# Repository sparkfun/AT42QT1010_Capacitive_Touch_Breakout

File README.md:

SparkFun Capacitive Touch Breakout - AT42QT101X
====================================

<table class="table table-hover table-striped table-bordered">
  <tr>
   <td><a href="https://www.sparkfun.com/products/12041"><div align="center"></div></a></td>
  <td><a href="https://www.sparkfun.com/products/14520"><div align="center"></div></a></center></td>
  </tr>
  <tr>
    <td><div align="center">SparkFun Capacitive Touch Breakout - AT42QT1010 [<a href="https://www.sparkfun.com/products/12041">SEN-12041</a>]</div></td>
    <td><div align="center">SparkFun Capacitive Touch Breakout - AT42QT1011 [<a href="https://www.sparkfun.com/products/14520">SEN-14520</a>]</div></td>
  </tr>
</table>

If you need to add user input without using a button, then a capacitive touch interface might be the answer. The AT42QT1010 and AT42QT1011 Capacitive Touch Breakout boards offer a single capacitive touch button with easy-to-use digital I/O pins. Each model features a slightly different output duration.

Repository Contents
-------------------
* **/Documentation** - Datasheet
* **/Firmware** - Example Arduino sketches
* **/Hardware** - All Eagle design files (.brd, .sch, .STL)
* **/Libraries** - Eagle part library
* **/Production** - Test bed files and production panel files

Documentation
-------------------

* **[Hookup Guide](https://learn.sparkfun.com/tutorials/at42qt101x-capacitive-touch-breakout-hookup-guide)** - Basic hookup guide for the AT42QT1010 and AT42QT1011 Capacitive Touch Breakout.
* *[Hookup Guide (RETIRED)](https://learn.sparkfun.com/tutorials/at42qt1010-capacitive-touch-breakout-hookup-guide) - Basic hookup guide for the AT42QT1010 Capacitive Touch Breakout.*
* **[SparkFun Fritzing repo](https://github.com/sparkfun/Fritzing_Parts)** - Fritzing diagrams for SparkFun products.

Version History
---------------
* **HW_v20.0_FW_v1.0** - Current Version for AT42QT1010 and AT42QT1011 with 8-pin UDFN/USON package.
* *[HW_v1.0_FW_v1.0 (RETIRED)](https://github.com/sparkfun/AT42QT1010_Capacitive_Touch_Breakout/releases/tag/HW_v1.0_FW_v1.0) - Initial release for the AT42QT1010 with 6-Pin SOT23-6 package.*

License Information
-------------------

This product is _**open source**_! 

Please review the LICENSE.md file for license information. 

If you have any questions or concerns on licensing, please contact techsupport@sparkfun.com.

Distributed as-is; no warranty is given.

- Your friends at SparkFun.

_<COLLABORATION CREDIT>_

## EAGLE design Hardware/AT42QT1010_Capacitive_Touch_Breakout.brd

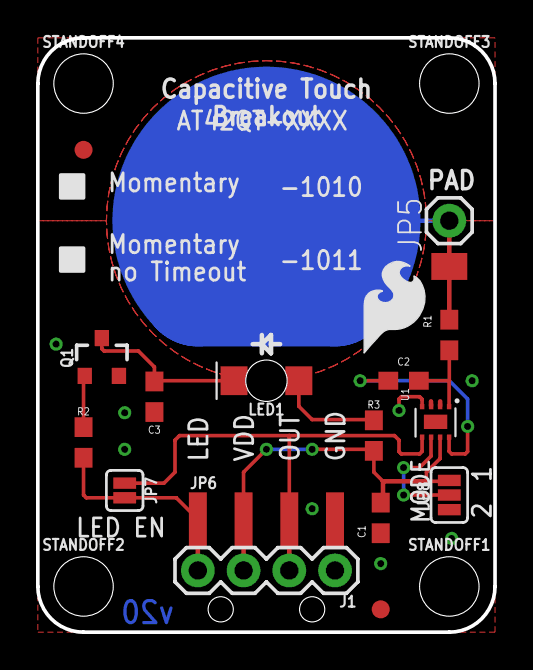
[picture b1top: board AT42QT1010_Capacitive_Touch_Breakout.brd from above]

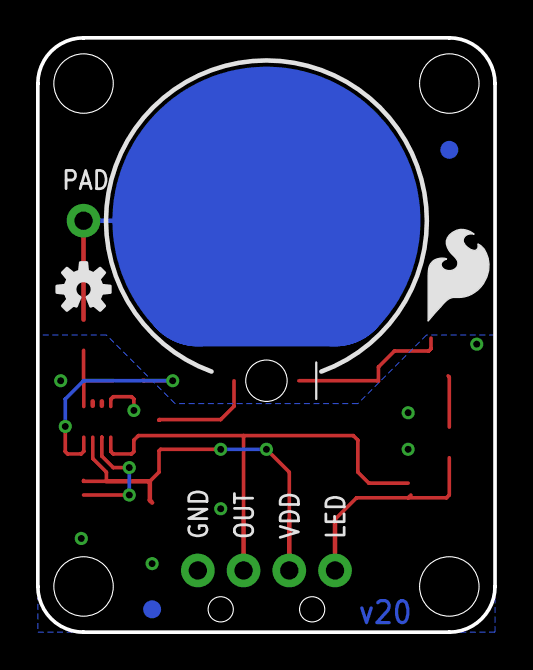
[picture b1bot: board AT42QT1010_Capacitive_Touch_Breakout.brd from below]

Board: 2 copper layers, 25.4 x 33.0 mm, 28 parts (4 on the bottom side), 11 nets.

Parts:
C1: 0.1uF; 0603
C2, C3: 10nF; 0603
FID1, FID2, FID3, FID4: FIDUCIAL1X2; FIDUCIAL-1X2
FRAME1: FRAME-LETTER; CREATIVE_COMMONS
J1: 1X04
JP5: 1X01
JP6: SMD; 1X04_SMD_RA_MALE
JP7: JUMPER-SMT_2_NC_PASTE_SILK; SMT-JUMPER_2_NC_PASTE_SILK
JP8: JUMPER-SMT_3_1-NC_PASTE_SILK; SMT-JUMPER_3_1-NC_PASTE_SILK
JP9: M01SMD-4.5X1.5; PAD-1.5X4.5
LED1: Green; LED-1206-BOTTOM
LOGO1, LOGO4: SFE_LOGO_FLAME.2_INCH; SFE_LOGO_FLAME_.2
LOGO2: OSHW-LOGOS; OSHW-LOGO-S
Q1: 600mA/40V; SOT23-3
R1: 10k; 0603
R2: 2.2k; 0603
R3: 200; 0603
STANDOFF1, STANDOFF2, STANDOFF3, STANDOFF4: STAND-OFF
U1: AT42QT1010 - UDFN; UDFN/USON_8_PAD
U$1: SPECIAL_INSTRUCTIONS-ORDERING; ORDERING_INSTRUCTIONS

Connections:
GND: C1.2, C3.2, J1.1, JP6.4, JP8.1, Q1.2, U1.4
LED: J1.4, JP6.1, JP7.2, R2.1
unnamed: JP8.2, U1.6
unnamed: C2.2, U1.8
unnamed: C2.1, R1.1, U1.1
unnamed: Q1.1, R2.2
unnamed: C3.1, LED1.C, Q1.3
unnamed: LED1.A, R3.1
OUT: J1.2, JP6.3, JP7.1, U1.5
PAD: JP5.1, JP9.P$1, R1.2
VCC: C1.1, J1.3, JP6.2, JP8.3, R3.2, U1.7

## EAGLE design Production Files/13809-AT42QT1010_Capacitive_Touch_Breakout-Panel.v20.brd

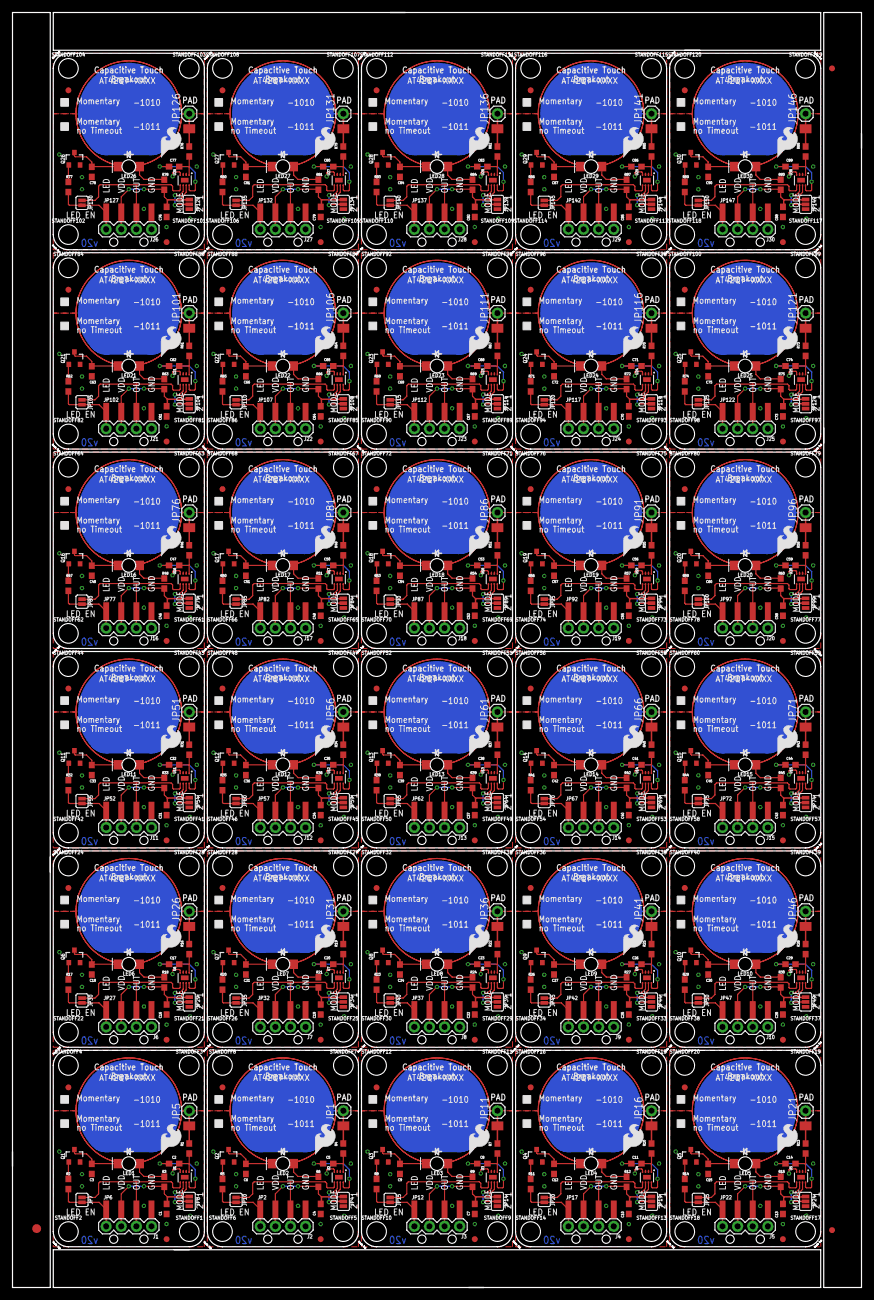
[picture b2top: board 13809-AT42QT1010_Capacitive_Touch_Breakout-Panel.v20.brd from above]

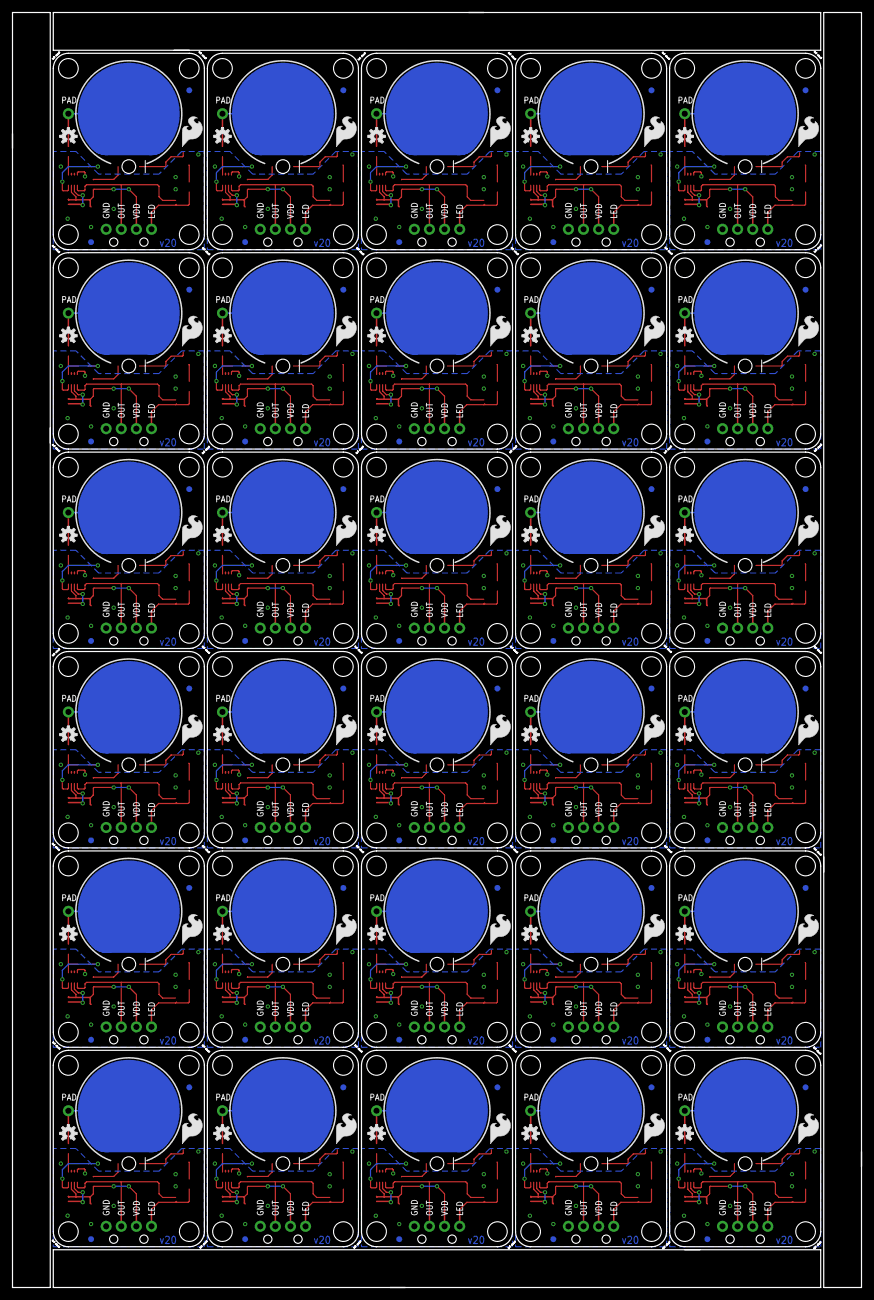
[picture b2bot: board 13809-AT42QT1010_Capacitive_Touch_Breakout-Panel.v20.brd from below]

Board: 2 copper layers, 142.7 x 214.4 mm, 783 parts (120 on the bottom side), 330 nets.

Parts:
C1, C4, C7, C10, C13, C16, C19, C22, C25, C28, C31, C34, C37, C40, C43, C46, C49, C52, C55, C58, C61, C64, C67, C70, C73, C76, C79, C82, C85, C88: 0.1uF; 0603
C2, C3, C5, C6, C8, C9, C11, C12, C14, C15, C17, C18, C20, C21, C23, C24, C26, C27, C29, C30, C32, C33, C35, C36, C38, C39, C41, C42, C44, C45, C47, C48, C50, C51, C53, C54, C56, C57, C59, C60, C62, C63, C65, C66, C68, C69, C71, C72, C74, C75, C77, C78, C80, C81, C83, C84, C86, C87, C89, C90: 10nF; 0603
E$1: FIDUCIAL-1.5X3
E$7, E$8: FIDUCIAL-1X2
FID1, FID2, FID3, FID4, FID5, FID6, FID7, FID8, FID9, FID10, FID11, FID12, FID13, FID14, FID15, FID16, FID17, FID18, FID19, FID20, FID21, FID22, FID23, FID24, FID25, FID26, FID27, FID28, FID29, FID30, FID31, FID32, FID33, FID34, FID35, FID36, FID37, FID38, FID39, FID40, FID41, FID42, FID43, FID44, FID45, FID46, FID47, FID48, FID49, FID50, FID51, FID52, FID53, FID54, FID55, FID56, FID57, FID58, FID59, FID60, FID61, FID62, FID63, FID64, FID65, FID66, FID67, FID68, FID69, FID70, FID71, FID72, FID73, FID74, FID75, FID76, FID77, FID78, FID79, FID80, FID81, FID82, FID83, FID84, FID85, FID86, FID87, FID88, FID89, FID90, FID91, FID92, FID93, FID94, FID95, FID96, FID97, FID98, FID99, FID100, FID101, FID102, FID103, FID104, FID105, FID106, FID107, FID108, FID109, FID110, FID111, FID112, FID113, FID114, FID115, FID116, FID117, FID118, FID119, FID120: FIDUCIAL1X2; FIDUCIAL-1X2
J1, J2, J3, J4, J5, J6, J7, J8, J9, J10, J11, J12, J13, J14, J15, J16, J17, J18, J19, J20, J21, J22, J23, J24, J25, J26, J27, J28, J29, J30: 1X04
JP1, JP5, JP11, JP16, JP21, JP26, JP31, JP36, JP41, JP46, JP51, JP56, JP61, JP66, JP71, JP76, JP81, JP86, JP91, JP96, JP101, JP106, JP111, JP116, JP121, JP126, JP131, JP136, JP141, JP146: 1X01
JP2, JP6, JP12, JP17, JP22, JP27, JP32, JP37, JP42, JP47, JP52, JP57, JP62, JP67, JP72, JP77, JP82, JP87, JP92, JP97, JP102, JP107, JP112, JP117, JP122, JP127, JP132, JP137, JP142, JP147: SMD; 1X04_SMD_RA_MALE
JP3, JP9, JP13, JP18, JP23, JP28, JP33, JP38, JP43, JP48, JP53, JP58, JP63, JP68, JP73, JP78, JP83, JP88, JP93, JP98, JP103, JP108, JP113, JP118, JP123, JP128, JP133, JP138, JP143, JP148: M01SMD-4.5X1.5; PAD-1.5X4.5
JP4, JP8, JP14, JP19, JP24, JP29, JP34, JP39, JP44, JP49, JP54, JP59, JP64, JP69, JP74, JP79, JP84, JP89, JP94, JP99, JP104, JP109, JP114, JP119, JP124, JP129, JP134, JP139, JP144, JP149: JUMPER-SMT_3_NO_SILK; SMT-JUMPER_3_NO_SILK
JP7, JP10, JP15, JP20, JP25, JP30, JP35, JP40, JP45, JP50, JP55, JP60, JP65, JP70, JP75, JP80, JP85, JP90, JP95, JP100, JP105, JP110, JP115, JP120, JP125, JP130, JP135, JP140, JP145, JP150: JUMPER-SMT_2_NO_SILK; SMT-JUMPER_2_NO_SILK
LED1, LED2, LED3, LED4, LED5, LED6, LED7, LED8, LED9, LED10, LED11, LED12, LED13, LED14, LED15, LED16, LED17, LED18, LED19, LED20, LED21, LED22, LED23, LED24, LED25, LED26, LED27, LED28, LED29, LED30: Green; LED-1206-BOTTOM
LOGO1, LOGO4, LOGO5, LOGO6, LOGO8, LOGO9, LOGO11, LOGO12, LOGO14, LOGO15, LOGO17, LOGO18, LOGO20, LOGO21, LOGO23, LOGO24, LOGO26, LOGO27, LOGO29, LOGO30, LOGO32, LOGO33, LOGO35, LOGO36, LOGO38, LOGO39, LOGO41, LOGO42, LOGO44, LOGO45, LOGO47, LOGO48, LOGO50, LOGO51, LOGO53, LOGO54, LOGO56, LOGO57, LOGO59, LOGO60, LOGO62, LOGO63, LOGO65, LOGO66, LOGO68, LOGO69, LOGO71, LOGO72, LOGO74, LOGO75, LOGO77, LOGO78, LOGO80, LOGO81, LOGO83, LOGO84, LOGO86, LOGO87, LOGO89, LOGO90: SFE_LOGO_FLAME.2_INCH; SFE_LOGO_FLAME_.2
LOGO2, LOGO3, LOGO7, LOGO10, LOGO13, LOGO16, LOGO19, LOGO22, LOGO25, LOGO28, LOGO31, LOGO34, LOGO37, LOGO40, LOGO43, LOGO46, LOGO49, LOGO52, LOGO55, LOGO58, LOGO61, LOGO64, LOGO67, LOGO70, LOGO73, LOGO76, LOGO79, LOGO82, LOGO85, LOGO88: OSHW-LOGOS; OSHW-LOGO-S
Q1, Q2, Q3, Q4, Q5, Q6, Q7, Q8, Q9, Q10, Q11, Q12, Q13, Q14, Q15, Q16, Q17, Q18, Q19, Q20, Q21, Q22, Q23, Q24, Q25, Q26, Q27, Q28, Q29, Q30: 600mA/40V; SOT23-3
R1, R4, R7, R10, R13, R16, R19, R22, R25, R28, R31, R34, R37, R40, R43, R46, R49, R52, R55, R58, R61, R64, R67, R70, R73, R76, R79, R82, R85, R88: 10k; 0603
R2, R5, R8, R11, R14, R17, R20, R23, R26, R29, R32, R35, R38, R41, R44, R47, R50, R53, R56, R59, R62, R65, R68, R71, R74, R77, R80, R83, R86, R89: 2.2k; 0603
R3, R6, R9, R12, R15, R18, R21, R24, R27, R30, R33, R36, R39, R42, R45, R48, R51, R54, R57, R60, R63, R66, R69, R72, R75, R78, R81, R84, R87, R90: 200; 0603
STANDOFF1, STANDOFF2, STANDOFF3, STANDOFF4, STANDOFF5, STANDOFF6, STANDOFF7, STANDOFF8, STANDOFF9, STANDOFF10, STANDOFF11, STANDOFF12, STANDOFF13, STANDOFF14, STANDOFF15, STANDOFF16, STANDOFF17, STANDOFF18, STANDOFF19, STANDOFF20, STANDOFF21, STANDOFF22, STANDOFF23, STANDOFF24, STANDOFF25, STANDOFF26, STANDOFF27, STANDOFF28, STANDOFF29, STANDOFF30, STANDOFF31, STANDOFF32, STANDOFF33, STANDOFF34, STANDOFF35, STANDOFF36, STANDOFF37, STANDOFF38, STANDOFF39, STANDOFF40, STANDOFF41, STANDOFF42, STANDOFF43, STANDOFF44, STANDOFF45, STANDOFF46, STANDOFF47, STANDOFF48, STANDOFF49, STANDOFF50, STANDOFF51, STANDOFF52, STANDOFF53, STANDOFF54, STANDOFF55, STANDOFF56, STANDOFF57, STANDOFF58, STANDOFF59, STANDOFF60, STANDOFF61, STANDOFF62, STANDOFF63, STANDOFF64, STANDOFF65, STANDOFF66, STANDOFF67, STANDOFF68, STANDOFF69, STANDOFF70, STANDOFF71, STANDOFF72, STANDOFF73, STANDOFF74, STANDOFF75, STANDOFF76, STANDOFF77, STANDOFF78, STANDOFF79, STANDOFF80, STANDOFF81, STANDOFF82, STANDOFF83, STANDOFF84, STANDOFF85, STANDOFF86, STANDOFF87, STANDOFF88, STANDOFF89, STANDOFF90, STANDOFF91, STANDOFF92, STANDOFF93, STANDOFF94, STANDOFF95, STANDOFF96, STANDOFF97, STANDOFF98, STANDOFF99, STANDOFF100, STANDOFF101, STANDOFF102, STANDOFF103, STANDOFF104, STANDOFF105, STANDOFF106, STANDOFF107, STANDOFF108, STANDOFF109, STANDOFF110, STANDOFF111, STANDOFF112, STANDOFF113, STANDOFF114, STANDOFF115, STANDOFF116, STANDOFF117, STANDOFF118, STANDOFF119, STANDOFF120: STAND-OFF
U1, U2, U3, U4, U5, U6, U7, U8, U9, U10, U11, U12, U13, U14, U15, U16, U17, U18, U19, U20, U21, U22, U23, U24, U25, U26, U27, U28, U29, U30: AT42QT1010 - UDFN; UDFN/USON_8_PAD

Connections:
GND: C1.2, C3.2, J1.1, JP6.4, JP8.3, Q1.2, U1.4
GND1: C4.2, C6.2, J2.1, JP2.4, JP4.3, Q2.2, U2.4
GND2: C7.2, C9.2, J3.1, JP12.4, JP14.3, Q3.2, U3.4
GND3: C10.2, C12.2, J4.1, JP17.4, JP19.3, Q4.2, U4.4
GND4: C13.2, C15.2, J5.1, JP22.4, JP24.3, Q5.2, U5.4
GND5: C16.2, C18.2, J6.1, JP27.4, JP29.3, Q6.2, U6.4
GND6: C19.2, C21.2, J7.1, JP32.4, JP34.3, Q7.2, U7.4
GND7: C22.2, C24.2, J8.1, JP37.4, JP39.3, Q8.2, U8.4
GND8: C25.2, C27.2, J9.1, JP42.4, JP44.3, Q9.2, U9.4
GND9: C28.2, C30.2, J10.1, JP47.4, JP49.3, Q10.2, U10.4
GND10: C31.2, C33.2, J11.1, JP52.4, JP54.3, Q11.2, U11.4
GND11: C34.2, C36.2, J12.1, JP57.4, JP59.3, Q12.2, U12.4
GND12: C37.2, C39.2, J13.1, JP62.4, JP64.3, Q13.2, U13.4
GND13: C40.2, C42.2, J14.1, JP67.4, JP69.3, Q14.2, U14.4
GND14: C43.2, C45.2, J15.1, JP72.4, JP74.3, Q15.2, U15.4
GND15: C46.2, C48.2, J16.1, JP77.4, JP79.3, Q16.2, U16.4
GND16: C49.2, C51.2, J17.1, JP82.4, JP84.3, Q17.2, U17.4
GND17: C52.2, C54.2, J18.1, JP87.4, JP89.3, Q18.2, U18.4
GND18: C55.2, C57.2, J19.1, JP92.4, JP94.3, Q19.2, U19.4
GND19: C58.2, C60.2, J20.1, JP97.4, JP99.3, Q20.2, U20.4
GND20: C61.2, C63.2, J21.1, JP102.4, JP104.3, Q21.2, U21.4
GND21: C64.2, C66.2, J22.1, JP107.4, JP109.3, Q22.2, U22.4
GND22: C67.2, C69.2, J23.1, JP112.4, JP114.3, Q23.2, U23.4
GND23: C70.2, C72.2, J24.1, JP117.4, JP119.3, Q24.2, U24.4
GND24: C73.2, C75.2, J25.1, JP122.4, JP124.3, Q25.2, U25.4
GND25: C76.2, C78.2, J26.1, JP127.4, JP129.3, Q26.2, U26.4
GND26: C79.2, C81.2, J27.1, JP132.4, JP134.3, Q27.2, U27.4
GND27: C82.2, C84.2, J28.1, JP137.4, JP139.3, Q28.2, U28.4
GND28: C85.2, C87.2, J29.1, JP142.4, JP144.3, Q29.2, U29.4
GND29: C88.2, C90.2, J30.1, JP147.4, JP149.3, Q30.2, U30.4
LED: J1.4, JP6.1, JP7.2, R2.1
LED1: J2.4, JP2.1, JP10.2, R5.1
LED2: J3.4, JP12.1, JP15.2, R8.1
LED3: J4.4, JP17.1, JP20.2, R11.1
LED4: J5.4, JP22.1, JP25.2, R14.1
LED5: J6.4, JP27.1, JP30.2, R17.1
LED6: J7.4, JP32.1, JP35.2, R20.1
LED7: J8.4, JP37.1, JP40.2, R23.1
LED8: J9.4, JP42.1, JP45.2, R26.1
LED9: J10.4, JP47.1, JP50.2, R29.1
LED10: J11.4, JP52.1, JP55.2, R32.1
LED11: J12.4, JP57.1, JP60.2, R35.1
LED12: J13.4, JP62.1, JP65.2, R38.1
LED13: J14.4, JP67.1, JP70.2, R41.1
LED14: J15.4, JP72.1, JP75.2, R44.1
LED15: J16.4, JP77.1, JP80.2, R47.1
LED16: J17.4, JP82.1, JP85.2, R50.1
LED17: J18.4, JP87.1, JP90.2, R53.1
LED18: J19.4, JP92.1, JP95.2, R56.1
LED19: J20.4, JP97.1, JP100.2, R59.1
LED20: J21.4, JP102.1, JP105.2, R62.1
LED21: J22.4, JP107.1, JP110.2, R65.1
LED22: J23.4, JP112.1, JP115.2, R68.1
LED23: J24.4, JP117.1, JP120.2, R71.1
LED24: J25.4, JP122.1, JP125.2, R74.1
LED25: J26.4, JP127.1, JP130.2, R77.1
LED26: J27.4, JP132.1, JP135.2, R80.1
LED27: J28.4, JP137.1, JP140.2, R83.1
LED28: J29.4, JP142.1, JP145.2, R86.1
LED29: J30.4, JP147.1, JP150.2, R89.1
unnamed: C5.2, U2.8
unnamed: C2.2, U1.8
unnamed: C2.1, R1.1, U1.1
unnamed: C5.1, R4.1, U2.1
unnamed: JP8.2, U1.6
unnamed: JP4.2, U2.6
unnamed: Q2.1, R5.2
unnamed: Q1.1, R2.2
unnamed: C3.1, LED1.C, Q1.3
unnamed: LED1.A, R3.1
unnamed: C6.1, LED2.C, Q2.3
unnamed: LED2.A, R6.1
unnamed: C8.2, U3.8
unnamed: C8.1, R7.1, U3.1
unnamed: JP14.2, U3.6
unnamed: Q3.1, R8.2
unnamed: C9.1, LED3.C, Q3.3
unnamed: LED3.A, R9.1
unnamed: C11.2, U4.8
unnamed: C11.1, R10.1, U4.1
unnamed: JP19.2, U4.6
unnamed: Q4.1, R11.2
unnamed: C12.1, LED4.C, Q4.3
unnamed: LED4.A, R12.1
unnamed: C14.2, U5.8
unnamed: C14.1, R13.1, U5.1
unnamed: JP24.2, U5.6
unnamed: Q5.1, R14.2
unnamed: C15.1, LED5.C, Q5.3
unnamed: LED5.A, R15.1
unnamed: C17.2, U6.8
unnamed: C17.1, R16.1, U6.1
unnamed: JP29.2, U6.6
unnamed: Q6.1, R17.2
unnamed: C18.1, LED6.C, Q6.3
unnamed: LED6.A, R18.1
unnamed: C20.2, U7.8
unnamed: C20.1, R19.1, U7.1
unnamed: JP34.2, U7.6
unnamed: Q7.1, R20.2
unnamed: C21.1, LED7.C, Q7.3
unnamed: LED7.A, R21.1
unnamed: C23.2, U8.8
unnamed: C23.1, R22.1, U8.1
unnamed: JP39.2, U8.6
unnamed: Q8.1, R23.2
unnamed: C24.1, LED8.C, Q8.3
unnamed: LED8.A, R24.1
unnamed: C26.2, U9.8
unnamed: C26.1, R25.1, U9.1
unnamed: JP44.2, U9.6
unnamed: Q9.1, R26.2
unnamed: C27.1, LED9.C, Q9.3
unnamed: LED9.A, R27.1
unnamed: C29.2, U10.8
unnamed: C29.1, R28.1, U10.1
unnamed: JP49.2, U10.6
unnamed: Q10.1, R29.2
unnamed: C30.1, LED10.C, Q10.3
unnamed: LED10.A, R30.1
unnamed: C32.2, U11.8
unnamed: C32.1, R31.1, U11.1
unnamed: JP54.2, U11.6
unnamed: Q11.1, R32.2
unnamed: C33.1, LED11.C, Q11.3
unnamed: LED11.A, R33.1
unnamed: C35.2, U12.8
unnamed: C35.1, R34.1, U12.1
unnamed: JP59.2, U12.6
unnamed: Q12.1, R35.2
unnamed: C36.1, LED12.C, Q12.3
unnamed: LED12.A, R36.1
unnamed: C38.2, U13.8
unnamed: C38.1, R37.1, U13.1
unnamed: JP64.2, U13.6
unnamed: Q13.1, R38.2
unnamed: C39.1, LED13.C, Q13.3
unnamed: LED13.A, R39.1
unnamed: C41.2, U14.8
unnamed: C41.1, R40.1, U14.1
unnamed: JP69.2, U14.6
unnamed: Q14.1, R41.2
unnamed: C42.1, LED14.C, Q14.3
unnamed: LED14.A, R42.1
unnamed: C44.2, U15.8
unnamed: C44.1, R43.1, U15.1
unnamed: JP74.2, U15.6
unnamed: Q15.1, R44.2
unnamed: C45.1, LED15.C, Q15.3
unnamed: LED15.A, R45.1
unnamed: C47.2, U16.8
unnamed: C47.1, R46.1, U16.1
unnamed: JP79.2, U16.6
unnamed: Q16.1, R47.2
unnamed: C48.1, LED16.C, Q16.3
unnamed: LED16.A, R48.1
unnamed: C50.2, U17.8
unnamed: C50.1, R49.1, U17.1
unnamed: JP84.2, U17.6
unnamed: Q17.1, R50.2
unnamed: C51.1, LED17.C, Q17.3
unnamed: LED17.A, R51.1
unnamed: C53.2, U18.8
unnamed: C53.1, R52.1, U18.1
unnamed: JP89.2, U18.6
unnamed: Q18.1, R53.2
unnamed: C54.1, LED18.C, Q18.3
unnamed: LED18.A, R54.1
unnamed: C56.2, U19.8
unnamed: C56.1, R55.1, U19.1
unnamed: JP94.2, U19.6
unnamed: Q19.1, R56.2
unnamed: C57.1, LED19.C, Q19.3
unnamed: LED19.A, R57.1
unnamed: C59.2, U20.8
unnamed: C59.1, R58.1, U20.1
unnamed: JP99.2, U20.6
unnamed: Q20.1, R59.2
unnamed: C60.1, LED20.C, Q20.3
unnamed: LED20.A, R60.1
unnamed: C62.2, U21.8
unnamed: C62.1, R61.1, U21.1
unnamed: JP104.2, U21.6
unnamed: Q21.1, R62.2
unnamed: C63.1, LED21.C, Q21.3
unnamed: LED21.A, R63.1
unnamed: C65.2, U22.8
unnamed: C65.1, R64.1, U22.1
unnamed: JP109.2, U22.6
unnamed: Q22.1, R65.2
unnamed: C66.1, LED22.C, Q22.3
unnamed: LED22.A, R66.1
unnamed: C68.2, U23.8
unnamed: C68.1, R67.1, U23.1
unnamed: JP114.2, U23.6
unnamed: Q23.1, R68.2
unnamed: C69.1, LED23.C, Q23.3
unnamed: LED23.A, R69.1
unnamed: C71.2, U24.8
unnamed: C71.1, R70.1, U24.1
unnamed: JP119.2, U24.6
unnamed: Q24.1, R71.2
unnamed: C72.1, LED24.C, Q24.3
unnamed: LED24.A, R72.1
unnamed: C74.2, U25.8
unnamed: C74.1, R73.1, U25.1
unnamed: JP124.2, U25.6
unnamed: Q25.1, R74.2
unnamed: C75.1, LED25.C, Q25.3
unnamed: LED25.A, R75.1
unnamed: C77.2, U26.8
unnamed: C77.1, R76.1, U26.1
unnamed: JP129.2, U26.6
unnamed: Q26.1, R77.2
unnamed: C78.1, LED26.C, Q26.3
unnamed: LED26.A, R78.1
unnamed: C80.2, U27.8
unnamed: C80.1, R79.1, U27.1
unnamed: JP134.2, U27.6
unnamed: Q27.1, R80.2
unnamed: C81.1, LED27.C, Q27.3
unnamed: LED27.A, R81.1
unnamed: C83.2, U28.8
unnamed: C83.1, R82.1, U28.1
unnamed: JP139.2, U28.6
unnamed: Q28.1, R83.2
unnamed: C84.1, LED28.C, Q28.3
unnamed: LED28.A, R84.1
unnamed: C86.2, U29.8
unnamed: C86.1, R85.1, U29.1
unnamed: JP144.2, U29.6
unnamed: Q29.1, R86.2
unnamed: C87.1, LED29.C, Q29.3
unnamed: LED29.A, R87.1
unnamed: C89.2, U30.8
unnamed: C89.1, R88.1, U30.1
unnamed: JP149.2, U30.6
unnamed: Q30.1, R89.2
unnamed: C90.1, LED30.C, Q30.3
unnamed: LED30.A, R90.1
OUT: J1.2, JP6.3, JP7.1, U1.5
OUT1: J2.2, JP2.3, JP10.1, U2.5
OUT2: J3.2, JP12.3, JP15.1, U3.5
OUT3: J4.2, JP17.3, JP20.1, U4.5
OUT4: J5.2, JP22.3, JP25.1, U5.5
OUT5: J6.2, JP27.3, JP30.1, U6.5
OUT6: J7.2, JP32.3, JP35.1, U7.5
OUT7: J8.2, JP37.3, JP40.1, U8.5
OUT8: J9.2, JP42.3, JP45.1, U9.5
OUT9: J10.2, JP47.3, JP50.1, U10.5
OUT10: J11.2, JP52.3, JP55.1, U11.5
OUT11: J12.2, JP57.3, JP60.1, U12.5
OUT12: J13.2, JP62.3, JP65.1, U13.5
OUT13: J14.2, JP67.3, JP70.1, U14.5
OUT14: J15.2, JP72.3, JP75.1, U15.5
OUT15: J16.2, JP77.3, JP80.1, U16.5
OUT16: J17.2, JP82.3, JP85.1, U17.5
OUT17: J18.2, JP87.3, JP90.1, U18.5
OUT18: J19.2, JP92.3, JP95.1, U19.5
OUT19: J20.2, JP97.3, JP100.1, U20.5
OUT20: J21.2, JP102.3, JP105.1, U21.5
OUT21: J22.2, JP107.3, JP110.1, U22.5
OUT22: J23.2, JP112.3, JP115.1, U23.5
OUT23: J24.2, JP117.3, JP120.1, U24.5
OUT24: J25.2, JP122.3, JP125.1, U25.5
OUT25: J26.2, JP127.3, JP130.1, U26.5
OUT26: J27.2, JP132.3, JP135.1, U27.5
OUT27: J28.2, JP137.3, JP140.1, U28.5
OUT28: J29.2, JP142.3, JP145.1, U29.5
OUT29: J30.2, JP147.3, JP150.1, U30.5
PAD: JP5.1, JP9.P$1, R1.2
PAD1: JP1.1, JP3.P$1, R4.2
PAD2: JP11.1, JP13.P$1, R7.2
PAD3: JP16.1, JP18.P$1, R10.2
PAD4: JP21.1, JP23.P$1, R13.2
PAD5: JP26.1, JP28.P$1, R16.2
PAD6: JP31.1, JP33.P$1, R19.2
PAD7: JP36.1, JP38.P$1, R22.2
PAD8: JP41.1, JP43.P$1, R25.2
PAD9: JP46.1, JP48.P$1, R28.2
PAD10: JP51.1, JP53.P$1, R31.2
PAD11: JP56.1, JP58.P$1, R34.2
PAD12: JP61.1, JP63.P$1, R37.2
PAD13: JP66.1, JP68.P$1, R40.2
PAD14: JP71.1, JP73.P$1, R43.2
PAD15: JP76.1, JP78.P$1, R46.2
PAD16: JP81.1, JP83.P$1, R49.2
PAD17: JP86.1, JP88.P$1, R52.2
PAD18: JP91.1, JP93.P$1, R55.2
PAD19: JP96.1, JP98.P$1, R58.2
PAD20: JP101.1, JP103.P$1, R61.2
PAD21: JP106.1, JP108.P$1, R64.2
PAD22: JP111.1, JP113.P$1, R67.2
PAD23: JP116.1, JP118.P$1, R70.2
PAD24: JP121.1, JP123.P$1, R73.2
PAD25: JP126.1, JP128.P$1, R76.2
PAD26: JP131.1, JP133.P$1, R79.2
PAD27: JP136.1, JP138.P$1, R82.2
PAD28: JP141.1, JP143.P$1, R85.2
PAD29: JP146.1, JP148.P$1, R88.2
VCC: C1.1, J1.3, JP6.2, JP8.1, R3.2, U1.7
VCC1: C4.1, J2.3, JP2.2, JP4.1, R6.2, U2.7
VCC2: C7.1, J3.3, JP12.2, JP14.1, R9.2, U3.7
VCC3: C10.1, J4.3, JP17.2, JP19.1, R12.2, U4.7
VCC4: C13.1, J5.3, JP22.2, JP24.1, R15.2, U5.7
VCC5: C16.1, J6.3, JP27.2, JP29.1, R18.2, U6.7
VCC6: C19.1, J7.3, JP32.2, JP34.1, R21.2, U7.7
VCC7: C22.1, J8.3, JP37.2, JP39.1, R24.2, U8.7
VCC8: C25.1, J9.3, JP42.2, JP44.1, R27.2, U9.7
VCC9: C28.1, J10.3, JP47.2, JP49.1, R30.2, U10.7
VCC10: C31.1, J11.3, JP52.2, JP54.1, R33.2, U11.7
VCC11: C34.1, J12.3, JP57.2, JP59.1, R36.2, U12.7
VCC12: C37.1, J13.3, JP62.2, JP64.1, R39.2, U13.7
VCC13: C40.1, J14.3, JP67.2, JP69.1, R42.2, U14.7
VCC14: C43.1, J15.3, JP72.2, JP74.1, R45.2, U15.7
VCC15: C46.1, J16.3, JP77.2, JP79.1, R48.2, U16.7
VCC16: C49.1, J17.3, JP82.2, JP84.1, R51.2, U17.7
VCC17: C52.1, J18.3, JP87.2, JP89.1, R54.2, U18.7
VCC18: C55.1, J19.3, JP92.2, JP94.1, R57.2, U19.7
VCC19: C58.1, J20.3, JP97.2, JP99.1, R60.2, U20.7
VCC20: C61.1, J21.3, JP102.2, JP104.1, R63.2, U21.7
VCC21: C64.1, J22.3, JP107.2, JP109.1, R66.2, U22.7
VCC22: C67.1, J23.3, JP112.2, JP114.1, R69.2, U23.7
VCC23: C70.1, J24.3, JP117.2, JP119.1, R72.2, U24.7
VCC24: C73.1, J25.3, JP122.2, JP124.1, R75.2, U25.7
VCC25: C76.1, J26.3, JP127.2, JP129.1, R78.2, U26.7
VCC26: C79.1, J27.3, JP132.2, JP134.1, R81.2, U27.7
VCC27: C82.1, J28.3, JP137.2, JP139.1, R84.2, U28.7
VCC28: C85.1, J29.3, JP142.2, JP144.1, R87.2, U29.7
VCC29: C88.1, J30.3, JP147.2, JP149.1, R90.2, U30.7

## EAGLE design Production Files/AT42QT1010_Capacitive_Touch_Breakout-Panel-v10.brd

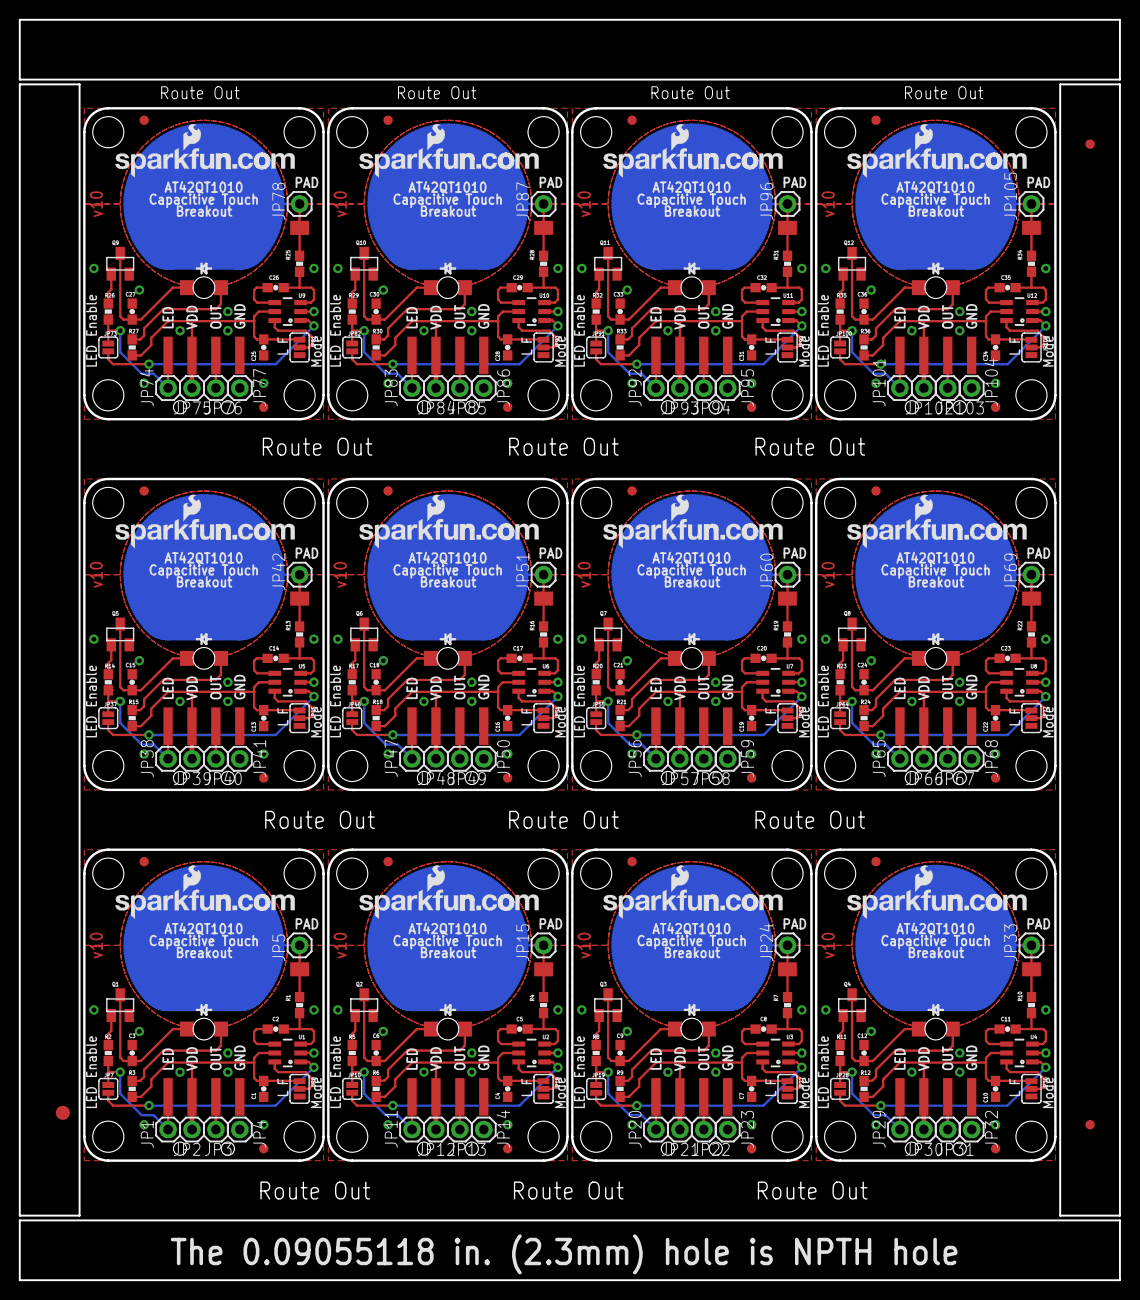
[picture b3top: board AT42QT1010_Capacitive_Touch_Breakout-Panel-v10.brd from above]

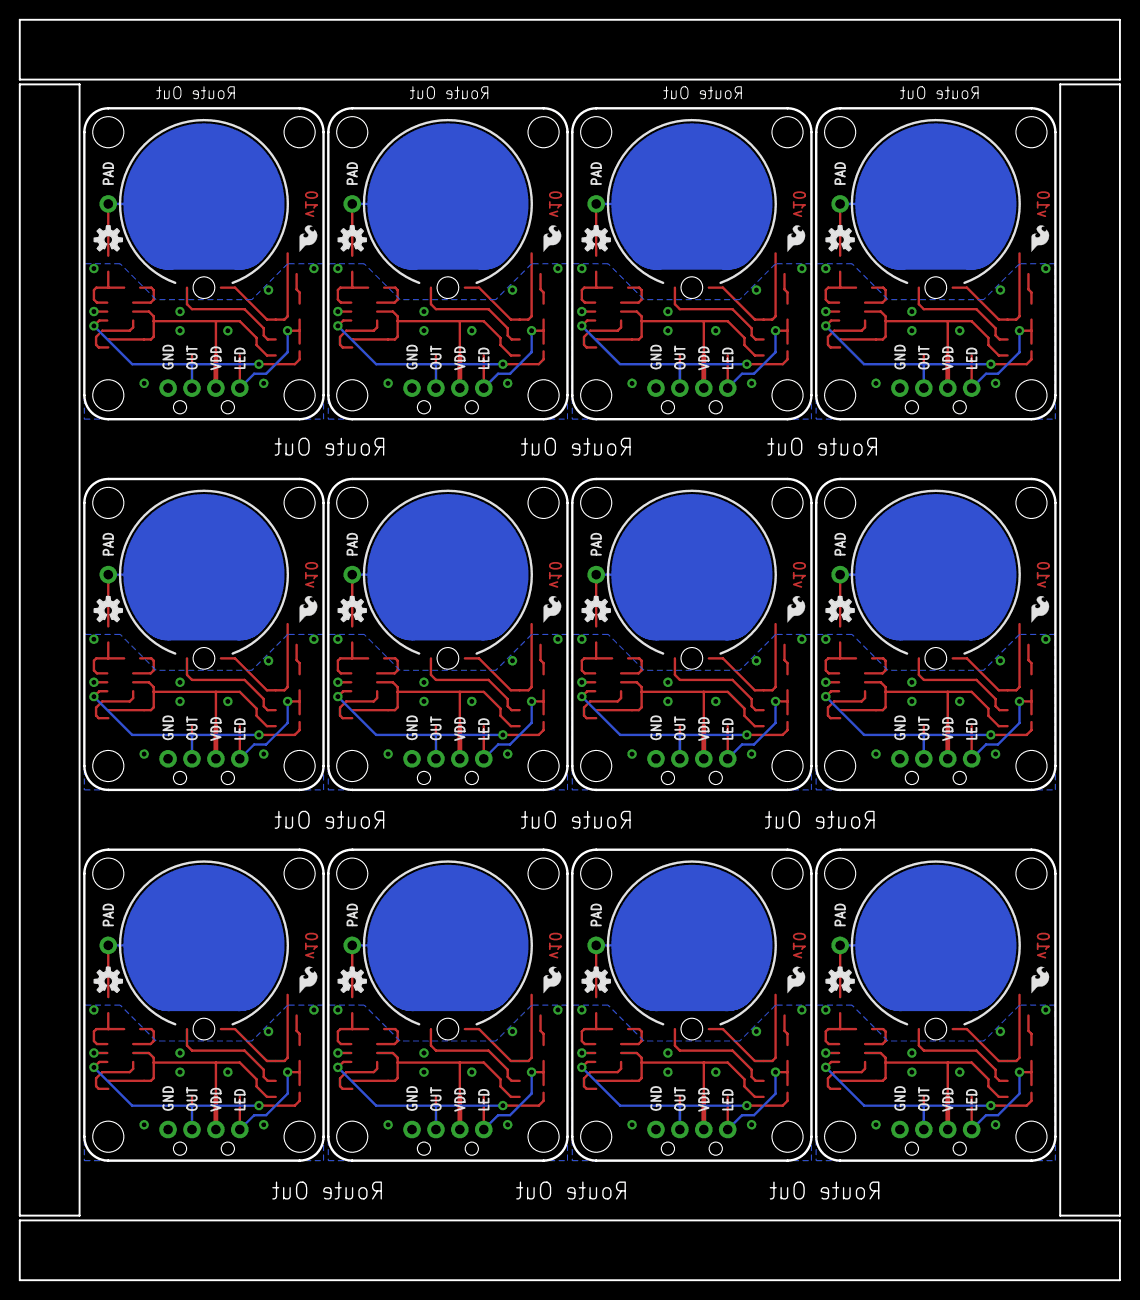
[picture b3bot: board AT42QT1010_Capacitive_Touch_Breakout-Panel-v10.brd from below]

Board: 2 copper layers, 116.8 x 133.8 mm, 327 parts (24 on the bottom side), 132 nets.

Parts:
C1, C4, C7, C10, C13, C16, C19, C22, C25, C28, C31, C34: 0.1uF; 0603-CAP
C2, C3, C5, C6, C8, C9, C11, C12, C14, C15, C17, C18, C20, C21, C23, C24, C26, C27, C29, C30, C32, C33, C35, C36: 10nF; 0603-CAP
E$1: FIDUCIAL-1.5X3
E$4, E$5: FIDUCIAL-1X2
FID1, FID2, FID3, FID4, FID5, FID6, FID7, FID8, FID9, FID10, FID11, FID12, FID13, FID14, FID15, FID16, FID17, FID18, FID19, FID20, FID21, FID22, FID23, FID24: FIDUCIAL1X2; FIDUCIAL-1X2
JP1, JP2, JP3, JP4, JP5, JP11, JP12, JP13, JP14, JP15, JP20, JP21, JP22, JP23, JP24, JP29, JP30, JP31, JP32, JP33, JP38, JP39, JP40, JP41, JP42, JP47, JP48, JP49, JP50, JP51, JP56, JP57, JP58, JP59, JP60, JP65, JP66, JP67, JP68, JP69, JP74, JP75, JP76, JP77, JP78, JP83, JP84, JP85, JP86, JP87, JP92, JP93, JP94, JP95, JP96, JP101, JP102, JP103, JP104, JP105: M01PTH; 1X01
JP6, JP16, JP25, JP34, JP43, JP52, JP61, JP70, JP79, JP88, JP97, JP106: SMD; 1X04-SMD_LONG
JP7, JP10, JP19, JP28, JP37, JP46, JP55, JP64, JP73, JP82, JP91, JP100: NC; SJ_2S
JP8, JP18, JP27, JP36, JP45, JP54, JP63, JP72, JP81, JP90, JP99, JP108: JUMPER-31-2; SJ_3_PASTE1&2
JP9, JP17, JP26, JP35, JP44, JP53, JP62, JP71, JP80, JP89, JP98, JP107: M01SMD-4.5X1.5; PAD-1.5X4.5
LED1, LED2, LED3, LED4, LED5, LED6, LED7, LED8, LED9, LED10, LED11, LED12: GREEN; LED-1206-BOTTOM
LOGO1, LOGO5, LOGO8, LOGO11, LOGO14, LOGO17, LOGO20, LOGO23, LOGO26, LOGO29, LOGO32, LOGO35: LOGO-SFENEW; SFE-NEW-WEBLOGO
LOGO2, LOGO4, LOGO7, LOGO10, LOGO13, LOGO16, LOGO19, LOGO22, LOGO25, LOGO28, LOGO31, LOGO34: OSHW-LOGOS; OSHW-LOGO-S
LOGO3, LOGO6, LOGO9, LOGO12, LOGO15, LOGO18, LOGO21, LOGO24, LOGO27, LOGO30, LOGO33, LOGO36: LOGO-SFESK; SFE-LOGO-FLAME
Q1, Q2, Q3, Q4, Q5, Q6, Q7, Q8, Q9, Q10, Q11, Q12: NPN; SOT23
R1, R4, R7, R10, R13, R16, R19, R22, R25, R28, R31, R34: 10k; 0603-RES
R2, R5, R8, R11, R14, R17, R20, R23, R26, R29, R32, R35: 2.2k; 0603-RES
R3, R6, R9, R12, R15, R18, R21, R24, R27, R30, R33, R36: 200; 0603-RES
STANDOFF1, STANDOFF2, STANDOFF3, STANDOFF4, STANDOFF5, STANDOFF6, STANDOFF7, STANDOFF8, STANDOFF9, STANDOFF10, STANDOFF11, STANDOFF12, STANDOFF13, STANDOFF14, STANDOFF15, STANDOFF16, STANDOFF17, STANDOFF18, STANDOFF19, STANDOFF20, STANDOFF21, STANDOFF22, STANDOFF23, STANDOFF24, STANDOFF25, STANDOFF26, STANDOFF27, STANDOFF28, STANDOFF29, STANDOFF30, STANDOFF31, STANDOFF32, STANDOFF33, STANDOFF34, STANDOFF35, STANDOFF36, STANDOFF37, STANDOFF38, STANDOFF39, STANDOFF40, STANDOFF41, STANDOFF42, STANDOFF43, STANDOFF44, STANDOFF45, STANDOFF46, STANDOFF47, STANDOFF48: STAND-OFF
U1, U2, U3, U4, U5, U6, U7, U8, U9, U10, U11, U12: AT42QT1010SOT23; SOT23-6

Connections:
GND: C1.2, C3.2, JP4.1, JP6.4, JP8.3, Q1.2, U1.2
GND1: C4.2, C6.2, JP14.1, JP16.4, JP18.3, Q2.2, U2.2
GND2: C7.2, C9.2, JP23.1, JP25.4, JP27.3, Q3.2, U3.2
GND3: C10.2, C12.2, JP32.1, JP34.4, JP36.3, Q4.2, U4.2
GND4: C13.2, C15.2, JP41.1, JP43.4, JP45.3, Q5.2, U5.2
GND5: C16.2, C18.2, JP50.1, JP52.4, JP54.3, Q6.2, U6.2
GND6: C19.2, C21.2, JP59.1, JP61.4, JP63.3, Q7.2, U7.2
GND7: C22.2, C24.2, JP68.1, JP70.4, JP72.3, Q8.2, U8.2
GND8: C25.2, C27.2, JP77.1, JP79.4, JP81.3, Q9.2, U9.2
GND9: C28.2, C30.2, JP86.1, JP88.4, JP90.3, Q10.2, U10.2
GND10: C31.2, C33.2, JP95.1, JP97.4, JP99.3, Q11.2, U11.2
GND11: C34.2, C36.2, JP104.1, JP106.4, JP108.3, Q12.2, U12.2
LED: JP1.1, JP6.1, JP7.2, R2.1
LED1: JP10.2, JP11.1, JP16.1, R5.1
LED2: JP19.2, JP20.1, JP25.1, R8.1
LED3: JP28.2, JP29.1, JP34.1, R11.1
LED4: JP37.2, JP38.1, JP43.1, R14.1
LED5: JP46.2, JP47.1, JP52.1, R17.1
LED6: JP55.2, JP56.1, JP61.1, R20.1
LED7: JP64.2, JP65.1, JP70.1, R23.1
LED8: JP73.2, JP74.1, JP79.1, R26.1
LED9: JP82.2, JP83.1, JP88.1, R29.1
LED10: JP91.2, JP92.1, JP97.1, R32.1
LED11: JP100.2, JP101.1, JP106.1, R35.1
unnamed: C5.2, U2.4
unnamed: C5.1, R4.1, U2.3
unnamed: JP18.2, U2.6
unnamed: C2.2, U1.4
unnamed: C2.1, R1.1, U1.3
unnamed: Q2.1, R5.2
unnamed: JP8.2, U1.6
unnamed: C6.1, LED2.C, Q2.3
unnamed: LED2.A, R6.1
unnamed: Q1.1, R2.2
unnamed: C3.1, LED1.C, Q1.3
unnamed: LED1.A, R3.1
unnamed: C8.2, U3.4
unnamed: C8.1, R7.1, U3.3
unnamed: JP27.2, U3.6
unnamed: Q3.1, R8.2
unnamed: C9.1, LED3.C, Q3.3
unnamed: LED3.A, R9.1
unnamed: C11.2, U4.4
unnamed: C11.1, R10.1, U4.3
unnamed: JP36.2, U4.6
unnamed: Q4.1, R11.2
unnamed: C12.1, LED4.C, Q4.3
unnamed: LED4.A, R12.1
unnamed: C14.2, U5.4
unnamed: C14.1, R13.1, U5.3
unnamed: JP45.2, U5.6
unnamed: Q5.1, R14.2
unnamed: C15.1, LED5.C, Q5.3
unnamed: LED5.A, R15.1
unnamed: C17.2, U6.4
unnamed: C17.1, R16.1, U6.3
unnamed: JP54.2, U6.6
unnamed: Q6.1, R17.2
unnamed: C18.1, LED6.C, Q6.3
unnamed: LED6.A, R18.1
unnamed: C20.2, U7.4
unnamed: C20.1, R19.1, U7.3
unnamed: JP63.2, U7.6
unnamed: Q7.1, R20.2
unnamed: C21.1, LED7.C, Q7.3
unnamed: LED7.A, R21.1
unnamed: C23.2, U8.4
unnamed: C23.1, R22.1, U8.3
unnamed: JP72.2, U8.6
unnamed: Q8.1, R23.2
unnamed: C24.1, LED8.C, Q8.3
unnamed: LED8.A, R24.1
unnamed: C26.2, U9.4
unnamed: C26.1, R25.1, U9.3
unnamed: JP81.2, U9.6
unnamed: Q9.1, R26.2
unnamed: C27.1, LED9.C, Q9.3
unnamed: LED9.A, R27.1
unnamed: C29.2, U10.4
unnamed: C29.1, R28.1, U10.3
unnamed: JP90.2, U10.6
unnamed: Q10.1, R29.2
unnamed: C30.1, LED10.C, Q10.3
unnamed: LED10.A, R30.1
unnamed: C32.2, U11.4
unnamed: C32.1, R31.1, U11.3
unnamed: JP99.2, U11.6
unnamed: Q11.1, R32.2
unnamed: C33.1, LED11.C, Q11.3
unnamed: LED11.A, R33.1
unnamed: C35.2, U12.4
unnamed: C35.1, R34.1, U12.3
unnamed: JP108.2, U12.6
unnamed: Q12.1, R35.2
unnamed: C36.1, LED12.C, Q12.3
unnamed: LED12.A, R36.1
OUT: JP3.1, JP6.3, JP7.1, U1.1
OUT1: JP10.1, JP13.1, JP16.3, U2.1
OUT2: JP19.1, JP22.1, JP25.3, U3.1
OUT3: JP28.1, JP31.1, JP34.3, U4.1
OUT4: JP37.1, JP40.1, JP43.3, U5.1
OUT5: JP46.1, JP49.1, JP52.3, U6.1
OUT6: JP55.1, JP58.1, JP61.3, U7.1
OUT7: JP64.1, JP67.1, JP70.3, U8.1
OUT8: JP73.1, JP76.1, JP79.3, U9.1
OUT9: JP82.1, JP85.1, JP88.3, U10.1
OUT10: JP91.1, JP94.1, JP97.3, U11.1
OUT11: JP100.1, JP103.1, JP106.3, U12.1
PAD: JP5.1, JP9.P$1, R1.2
PAD1: JP15.1, JP17.P$1, R4.2
PAD2: JP24.1, JP26.P$1, R7.2
PAD3: JP33.1, JP35.P$1, R10.2
PAD4: JP42.1, JP44.P$1, R13.2
PAD5: JP51.1, JP53.P$1, R16.2
PAD6: JP60.1, JP62.P$1, R19.2
PAD7: JP69.1, JP71.P$1, R22.2
PAD8: JP78.1, JP80.P$1, R25.2
PAD9: JP87.1, JP89.P$1, R28.2
PAD10: JP96.1, JP98.P$1, R31.2
PAD11: JP105.1, JP107.P$1, R34.2
VCC: C1.1, JP2.1, JP6.2, JP8.1, R3.2, U1.5
VCC1: C4.1, JP12.1, JP16.2, JP18.1, R6.2, U2.5
VCC2: C7.1, JP21.1, JP25.2, JP27.1, R9.2, U3.5
VCC3: C10.1, JP30.1, JP34.2, JP36.1, R12.2, U4.5
VCC4: C13.1, JP39.1, JP43.2, JP45.1, R15.2, U5.5
VCC5: C16.1, JP48.1, JP52.2, JP54.1, R18.2, U6.5
VCC6: C19.1, JP57.1, JP61.2, JP63.1, R21.2, U7.5
VCC7: C22.1, JP66.1, JP70.2, JP72.1, R24.2, U8.5
VCC8: C25.1, JP75.1, JP79.2, JP81.1, R27.2, U9.5
VCC9: C28.1, JP84.1, JP88.2, JP90.1, R30.2, U10.5
VCC10: C31.1, JP93.1, JP97.2, JP99.1, R33.2, U11.5
VCC11: C34.1, JP102.1, JP106.2, JP108.1, R36.2, U12.5

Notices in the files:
parts and their libraries:
SparkFun-Aesthetics: Licensing: CC v3.0 Share-Alike You are welcome to use this library for commercial purposes.
SparkFun-Aesthetics: Released under the Creative Commons Attribution Share-Alike 4.0 License
SparkFun-Aesthetics: https://creativecommons.org/licenses/by-sa/4.0
